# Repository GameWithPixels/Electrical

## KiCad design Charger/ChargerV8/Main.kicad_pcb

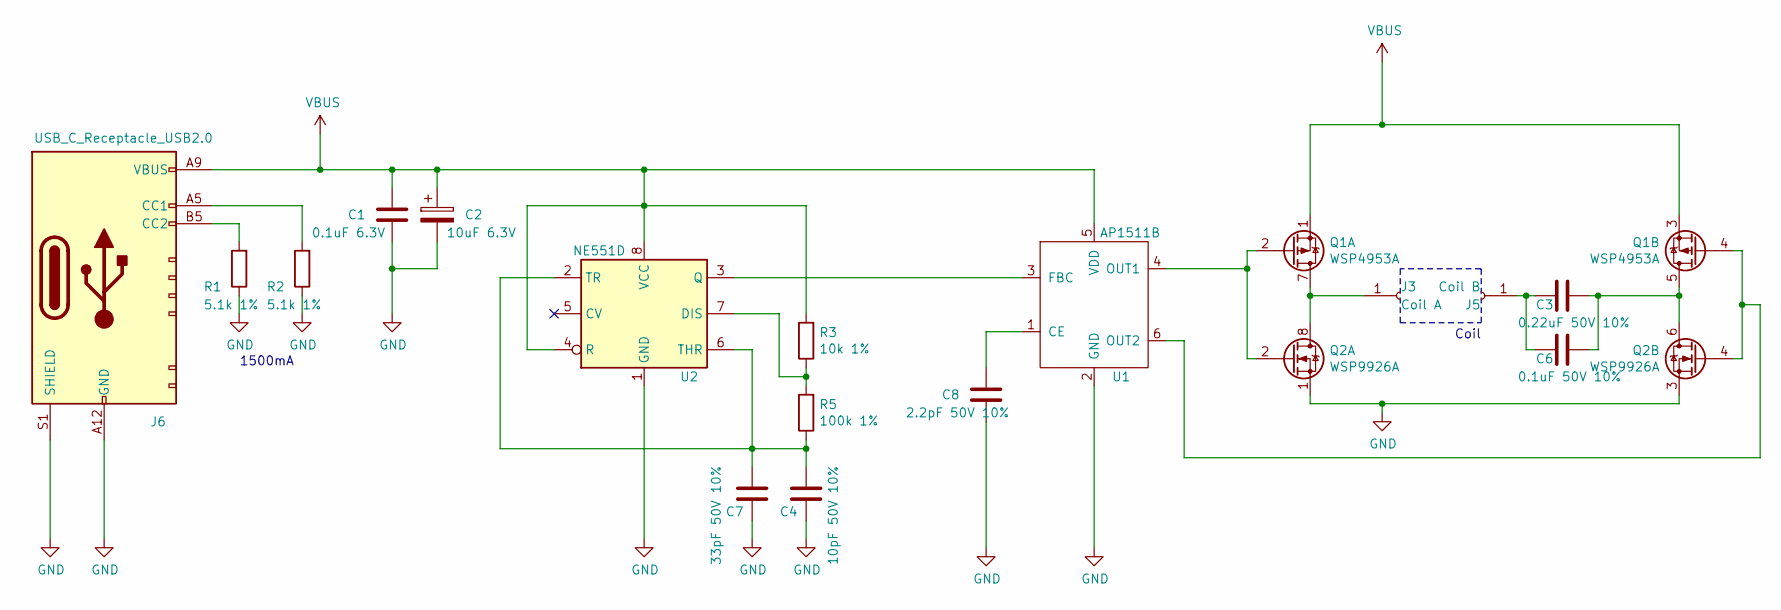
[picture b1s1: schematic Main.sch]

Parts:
C1: 0.1uF 6.3V; C_0603_1608Metric; Part Number TCC0603X7R104K500CT; LCSC Part Number C282519
C2: 10uF 6.3V; C_0603_1608Metric; Part Number CL10A106MP8NNNC; LCSC Part Number C85713
C3: 0.22uF 50V 10%; C_0805_2012Metric; Part Number CL21B224KBFNNNE; LCSC Part Number C5378
C4: 10pF 50V 10%; C_0603_1608Metric; Part Number CL10C100JB8NNNC; LCSC Part Number C1634
C6: 0.1uF 50V 10%; C_0805_2012Metric; Part Number CL21B104JBCNNNC; LCSC Part Number C62912
C7: 33pF 50V 10%; C_0603_1608Metric; Part Number CL10C330JB8NNNC; LCSC Part Number C1663
C8: 2.2pF 50V 10%; C_0603_1608Metric; Part Number CL10C2R2CB8NNNC; LCSC Part Number C84711
J3: Coil A; TestPoint_THTPad_D2.0mm_Drill1.0mm
J5: Coil B; TestPoint_THTPad_D2.0mm_Drill1.0mm
J6: USB_C_Receptacle_USB2.0; USB-C-SMD_10P-P1.00-L6.8-W8.9; Part Number TYPE-C-31-M-17; LCSC Part Number C283540
Q1: WSP4953A; SOP-8_3.9x4.9mm_P1.27mm; LCSC Part Number C148415
Q2: WSP9926A; SOP-8_3.9x4.9mm_P1.27mm; LCSC Part Number C86339
R1, R2: 5.1k 1%; R_0603_1608Metric; LCSC Part Number C23186
R3: 10k 1%; R_0603_1608Metric; LCSC Part Number C25804
R5: 100k 1%; R_0603_1608Metric; LCSC Part Number C25803
U1: AP1511B; SOT-26; LCSC Part Number C347457
U2: NE551D; SOP-8_3.9x4.9mm_P1.27mm; Part Number XL551; LCSC Part Number C707074

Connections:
GND: C1.2, C2.2, C4.2, C7.2, C8.2, J6.A12 (GND), J6.B12 (GND), J6.S1 (SHIELD), Q2.1 (S), Q2.3 (S), R1.1, R2.1, U1.2 (GND), U2.1 (GND)
unnamed: C3.1, C6.1, Q1.5 (D), Q1.6 (D), Q2.5 (D), Q2.6 (D)
unnamed: C3.2, C6.2, J5.1
unnamed: C4.1, C7.1, R5.1, U2.2 (TR), U2.6 (THR)
unnamed: C8.1, U1.1 (CE)
unnamed: J3.1, Q1.7 (D), Q1.8 (D), Q2.7 (D), Q2.8 (D)
unnamed: J6.A5 (CC1), R2.2
unnamed: J6.B5 (CC2), R1.2
unnamed: Q1.2 (G), Q2.2 (G), U1.4 (OUT1)
unnamed: Q1.4 (G), Q2.4 (G), U1.6 (OUT2)
unnamed: R3.1, R5.2, U2.7 (DIS)
unnamed: U1.3 (FBC), U2.3 (Q)
VBUS: C1.1, C2.1, J6.A9 (VBUS), J6.B9 (VBUS), Q1.1 (S), Q1.3 (S), R3.2, U1.5 (VDD), U2.4 (R), U2.8 (VCC)

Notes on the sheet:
1500mA
Coil

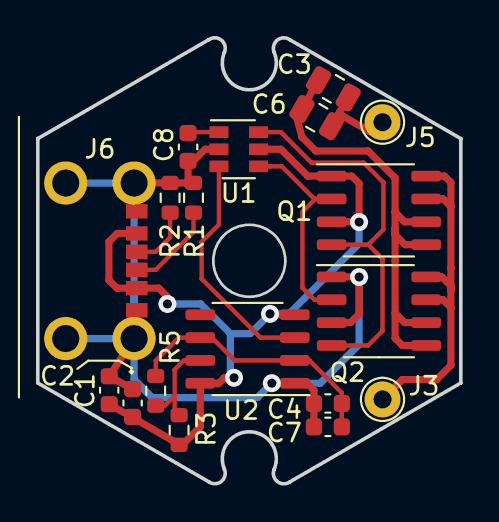
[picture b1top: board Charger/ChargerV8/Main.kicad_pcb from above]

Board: 2 copper layers, 23.5 x 24.8 mm, 18 parts (0 on the bottom side), 13 nets.

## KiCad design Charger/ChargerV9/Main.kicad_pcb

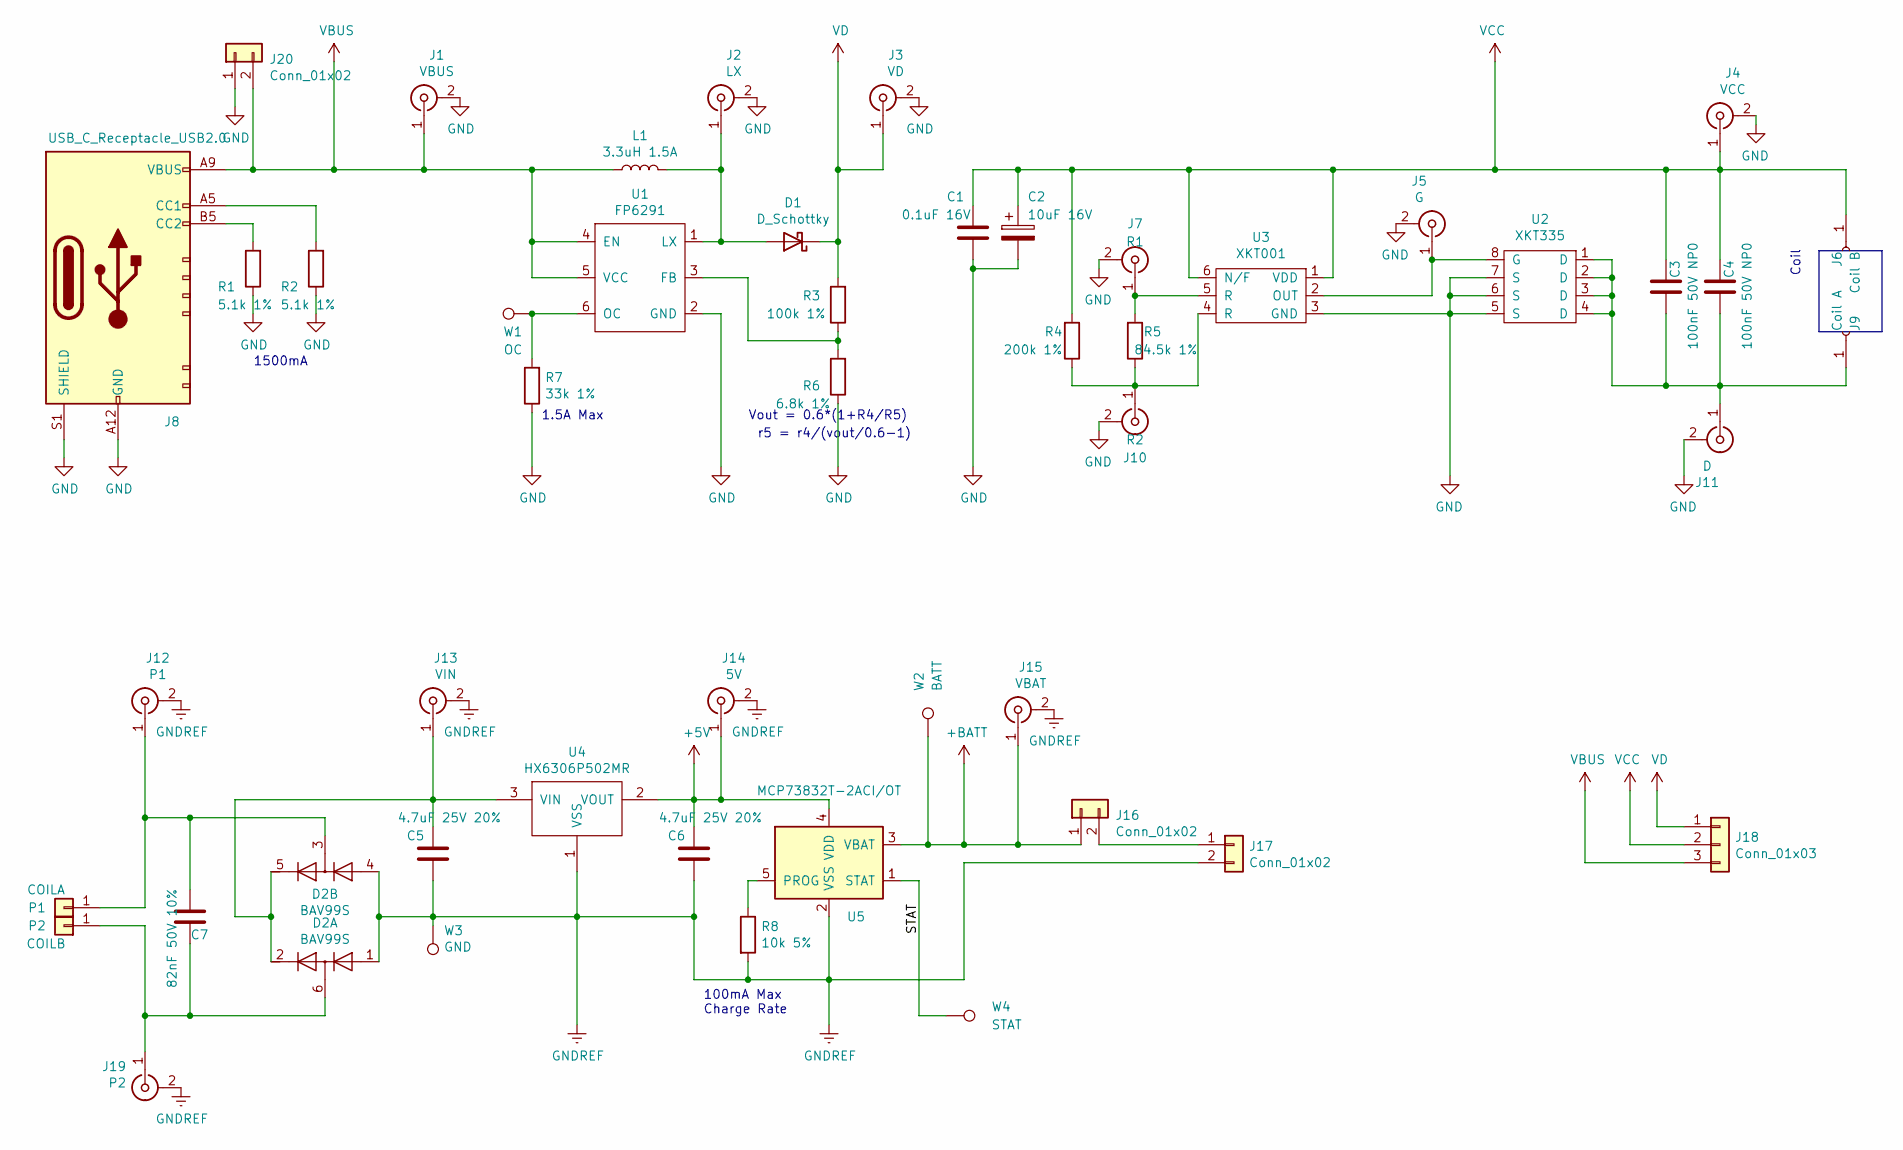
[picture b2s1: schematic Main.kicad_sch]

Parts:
C1: 0.1uF 16V; C_0402_1005Metric; Part Number C1005X5R1H104KT000F; LCSC Part Number C361202
C2: 10uF 16V; C_0805_2012Metric; LCSC Part Number C89827
C3, C4: 100nF 50V NP0; C_1206_3216Metric; Part Number 1206N104J500CT; LCSC Part Number C170182
C5, C6: 4.7uF 25V 20%; C_0805_2012Metric; Part Number CL21A475KAQNNNE; LCSC Part Number C1779
C7: 82nF 50V 10%; C_0805_2012Metric; Part Number CC0603KRX7R9BB823; LCSC Part Number C107100
D1: D_Schottky; D_SOD-123; Part Number B5819W; LCSC Part Number C8598
D2: BAV99S; SOT-363_SC-70-6; Part Number BAV99SH6327XTSA1; LCSC Part Number C68987
J1: VBUS; U.FL-R-SMT-1(80); Part Number U.FL-R-SMT-1(80); LCSC Part Number C88374
J2: LX; U.FL-R-SMT-1(80); Part Number U.FL-R-SMT-1(80); LCSC Part Number C88374
J3: VD; U.FL-R-SMT-1(80); Part Number U.FL-R-SMT-1(80); LCSC Part Number C88374
J4: VCC; U.FL-R-SMT-1(80); Part Number U.FL-R-SMT-1(80); LCSC Part Number C88374
J5: G; U.FL-R-SMT-1(80); Part Number U.FL-R-SMT-1(80); LCSC Part Number C88374
J6: Coil B; TestPoint_THTPad_D2.0mm_Drill1.0mm
J7: R1; U.FL-R-SMT-1(80); Part Number U.FL-R-SMT-1(80); LCSC Part Number C88374
J8: USB_C_Receptacle_USB2.0; USB-C-SMD_10P-P1.00-L6.8-W8.9; Part Number TYPE-C-31-M-17; LCSC Part Number C283540
J9: Coil A; TestPoint_THTPad_D2.0mm_Drill1.0mm
J10: R2; U.FL-R-SMT-1(80); Part Number U.FL-R-SMT-1(80); LCSC Part Number C88374
J11: D; U.FL-R-SMT-1(80); Part Number U.FL-R-SMT-1(80); LCSC Part Number C88374
J12: P1; U.FL-R-SMT-1(80); Part Number U.FL-R-SMT-1(80); LCSC Part Number C88374
J13: VIN; U.FL-R-SMT-1(80); Part Number U.FL-R-SMT-1(80); LCSC Part Number C88374
J14: 5V; U.FL-R-SMT-1(80); Part Number U.FL-R-SMT-1(80); LCSC Part Number C88374
J15: VBAT; U.FL-R-SMT-1(80); Part Number U.FL-R-SMT-1(80); LCSC Part Number C88374
J16, J20: Conn_01x02; PinHeader_1x02_P2.54mm_Vertical
J17: Conn_01x02; Hongjie 10100 Connector
J18: Conn_01x03; PinHeader_1x03_P2.54mm_Vertical
J19: P2; U.FL-R-SMT-1(80); Part Number U.FL-R-SMT-1(80); LCSC Part Number C88374
L1: 3.3uH 1.5A; L_1008_2520Metric; Part Number MPH252010C3R3MT; LCSC Part Number C370029
P1: COILA; TestPoint_THTPad_D1.5mm_Drill0.7mm
P2: COILB; TestPoint_THTPad_D1.5mm_Drill0.7mm
R1, R2: 5.1k 1%; R_0402_1005Metric; Part Number RC0402FR-075K1L; LCSC Part Number C105872
R3: 100k 1%; R_0402_1005Metric; Part Number 0402WGF1003TCE; LCSC Part Number C25741
R4: 200k 1%; R_0603_1608Metric; Part Number 0603WAF2003T5E; LCSC Part Number C25811
R5: 84.5k 1%; R_0603_1608Metric; Part Number ERJ3EKF8452V; LCSC Part Number C403376
R6: 6.8k 1%; R_0402_1005Metric; Part Number 0402WGF6801TCE; LCSC Part Number C25917
R7: 33k 1%; R_0402_1005Metric; Part Number 0402WGF3302TCE; LCSC Part Number C25779
R8: 10k 5%; R_0402_1005Metric; Part Number RC0402FR-0710KL; LCSC Part Number C60490
U1: FP6291; SOT-23-6; Part Number FP6291LR-G1; LCSC Part Number C18701
U2: XKT335; SO-8_3.9x4.9mm_P1.27mm
U3: XKT001; SOT-23-6
U4: HX6306P502MR; SOT-23; Part Number HX6306P502MR; LCSC Part Number C296209
U5: MCP73832T-2ACI/OT; SOT-23-5; Part Number MCP73832T-2ACI/OT; LCSC Part Number C38066
W1: OC; TestPoint_Pad_1.0x1.0mm
W2: BATT; TestPoint_Pad_1.0x1.0mm
W3: GND; TestPoint_Pad_1.0x1.0mm
W4: STAT; TestPoint_Pad_1.0x1.0mm

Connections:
+5V: C6.1, J14.1 (In), U4.2 (VOUT), U5.4 (VDD)
+BATT: J15.1 (In), J16.1, U5.3 (VBAT), W2.1
/STAT: U5.1 (STAT), W4.1
GND: C1.2, C2.2, J1.2 (Ext), J2.2 (Ext), J3.2 (Ext), J4.2 (Ext), J5.2 (Ext), J7.2 (Ext), J8.A12 (GND), J8.B12 (GND), J8.S1 (SHIELD), J10.2 (Ext), J11.2 (Ext), J20.1, R1.1, R2.1, R6.1, R7.1, U1.2 (GND), U2.5 (S), U2.6 (S), U2.7 (S), U3.3 (GND)
GNDREF: C5.2, C6.2, D2.1 (A1), D2.4 (A3), J12.2 (Ext), J13.2 (Ext), J14.2 (Ext), J15.2 (Ext), J17.2, J19.2 (Ext), R8.2, U4.1 (VSS), U5.2 (VSS), W3.1
unnamed: C3.1, C4.1, J9.1, J11.1 (In), U2.1 (D), U2.2 (D), U2.3 (D), U2.4 (D)
unnamed: C5.1, D2.2 (K2), D2.5 (K4), J13.1 (In), U4.3 (VIN)
unnamed: C7.1, D2.3 (K1A2), J12.1 (In), P1.1
unnamed: C7.2, D2.6 (K3A4), J19.1 (In), P2.1
unnamed: D1.2 (A), J2.1 (In), L1.2, U1.1 (LX)
unnamed: J5.1 (In), U2.8 (G), U3.2 (OUT)
unnamed: J7.1 (In), R5.2, U3.5 (R)
unnamed: J8.A5 (CC1), R2.2
unnamed: J8.B5 (CC2), R1.2
unnamed: J10.1 (In), R4.1, R5.1, U3.4 (R)
unnamed: J16.2, J17.1
unnamed: R3.1, R6.2, U1.3 (FB)
unnamed: R7.2, U1.6 (OC), W1.1
unnamed: R8.1, U5.5 (PROG)
VBUS: J1.1 (In), J8.A9 (VBUS), J8.B9 (VBUS), J18.3, J20.2, L1.1, U1.4 (EN), U1.5 (VCC)
VCC: C1.1, C2.1, C3.2, C4.2, J4.1 (In), J6.1, J18.2, R4.2, U3.1 (VDD), U3.6 (N/F)
VD: D1.1 (K), J3.1 (In), J18.1, R3.2

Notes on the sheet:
r5 = r4/(vout/0.6-1)
100mA Max Charge Rate
1.5A Max
1500mA
Vout = 0.6*(1+R4/R5)
Coil

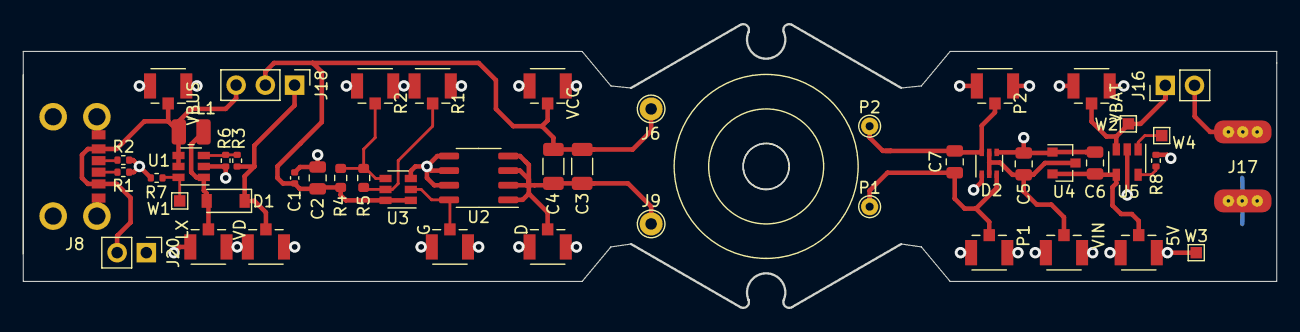
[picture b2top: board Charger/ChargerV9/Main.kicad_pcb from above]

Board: 2 copper layers, 109.0 x 24.7 mm, 49 parts (0 on the bottom side), 22 nets.

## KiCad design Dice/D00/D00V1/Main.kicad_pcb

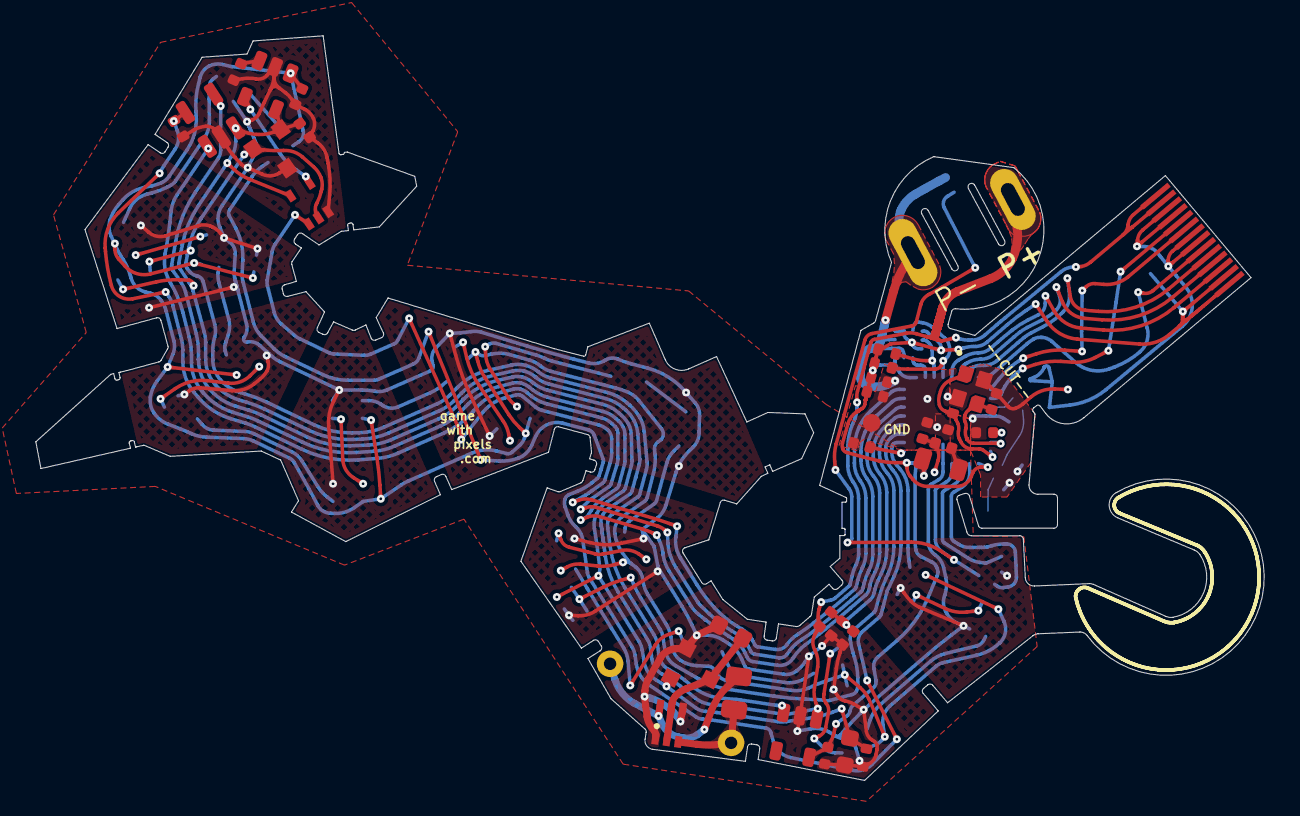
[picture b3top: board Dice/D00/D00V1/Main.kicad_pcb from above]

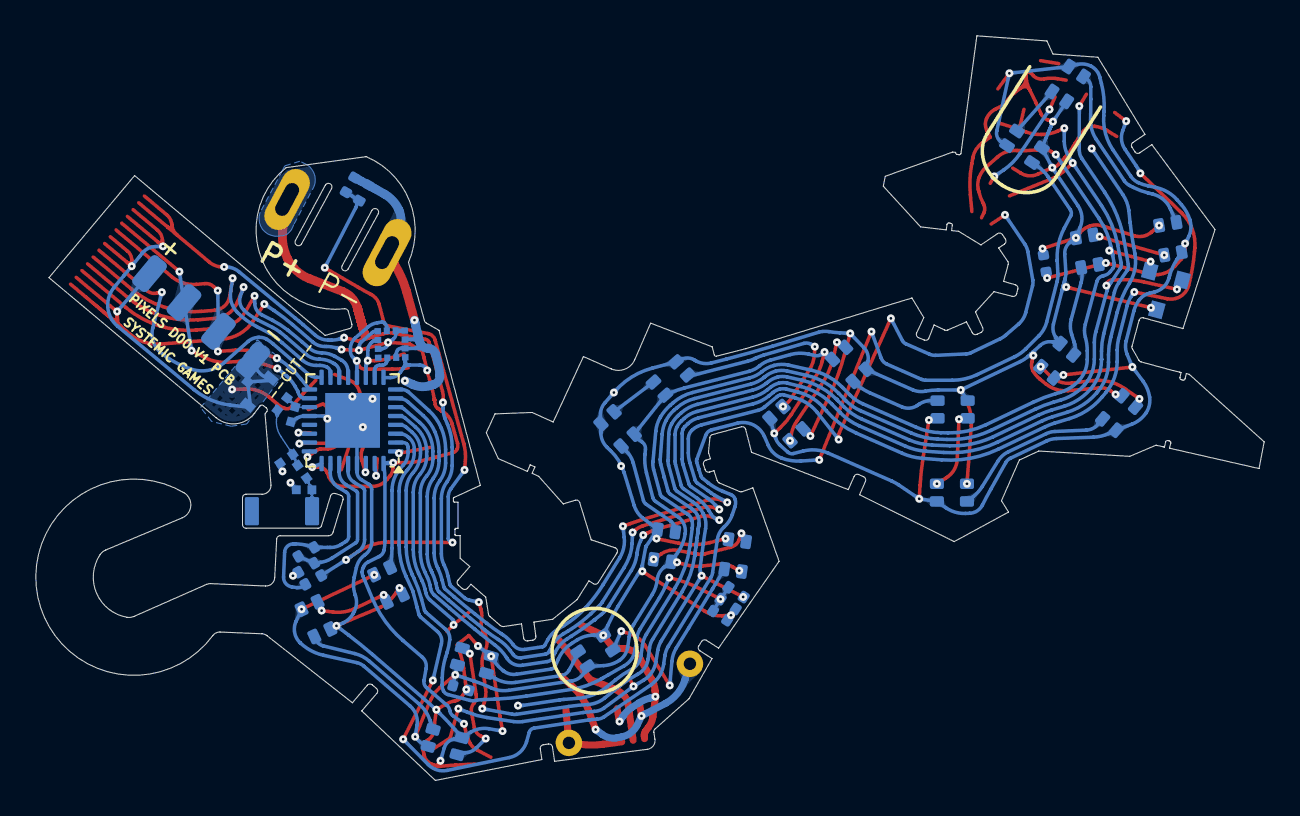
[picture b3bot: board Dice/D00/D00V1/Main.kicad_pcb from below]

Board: 2 copper layers, 69.4 x 42.1 mm, 76 parts (43 on the bottom side), 58 nets.

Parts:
AE1: Antenna_Chip; CHIP_ANT
C1, C4, C18: 4.7uF 10V 20%; C_0402_1005Metric
C2, C5: 8pF 10V 10%; C_0402_1005Metric
C3, C10, C23, C24: 0.1uF 10V 20%; C_0402_1005Metric
C6: DNP; C_0402_1005Metric
C7: 100pF NP0 10V 5%; C_0402_1005Metric
C8: 0.8pF 10V 5% C0G; 0402_RF
C9, C16: 10uF 10V 20%; C_0402_1005Metric
C11, C12: DNP; 0402_RF
C13: 4.7uF 25V 20%; C_0603_1608Metric
C15: 22uF 10V 20%; C_0603_1608Metric
C19: 12nF 50V 5% NP0; C_0805_2012Metric
C21, C22: 10nF 25V 10%; C_0402_1005Metric
D1: BAV99S; SOT-363_SC-70-6
D2, D3, D4, D5, D6, D7, D8, D9, D10, D11, D12, D13, D14, D15, D16, D17, D18, D20, D21: TX1812Z_2020
J1: Conn_01x14; FPC_14
J2: Conn_01x04; FPC-POGO-4
J3: Conn_01x02; Hongjie 10100 Connector
J4: DNP; MFH3.RECE.20369.001E.01
L1: 10uH 100mA 20%; L_0805_2012Metric
L2: 15nH 100mA 5%; L_0402_1005Metric
L3: 0 Ohm; 0402_RF
L5: 3.9nH 5%; 0402_RF
P5: COILA; TestPoint_THTPad_D1.5mm_Drill0.7mm
P6: COILB; TestPoint_THTPad_D1.5mm_Drill0.7mm
R1, R2, R7: 4.02M 1%; R_0402_1005Metric
R3: 10k 5%; R_0402_1005Metric
R4, R5, R10: 100k 1%; R_0402_1005Metric
R6: 22k 1%; R_0402_1005Metric
R8: 10M 1%; R_0402_1005Metric
R9: 220k 1%; R_0402_1005Metric
R12, R16: 2.7k 5%; R_0402_1005Metric
TH1: NTC 100k @ 25C; R_0402_1005Metric
U1: N52810_QFN32; QFN-32-1EP_5x5mm_P0.5mm_EP3.1x3.1mm
U2: KXTJ3-1057; LGA-12_2x2mm_P0.5mm
U3: PJ75BL50SA; SOT-23
U4: ME6215; SOT-23-5
U5: MCP73832T-2ACI/OT; SOT-23-5
U6: MT9700; SOT-23-5
U7: SN74LVC1G08; SOT-353_SC-70-5
U8, U8-alt1: VCS2373S; SOT-23
W19: GND; TEST_PIN
Y1: 32MHz 40ppm; Crystal_SMD_2016-4Pin_2.0x1.6mm

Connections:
+5V: C15.1, R1.1, R4.1, U3.2 (VOUT), U5.4 (VDD)
+BATT: C16.1, J1.1, J1.2, J3.1, R7.1, U4.1 (VIN), U5.3 (VBAT), U6.5 (VIN), U7.5 (VCC), U8.1 (VCC), U8-alt1.1 (VCC)
/5V_SENSE: C21.1, R1.2, R2.2, U1.4 (P0.04/AIN2)
/ACC_INT: U1.10 (P0.12), U2.5 (INT)
/ANTENNA: AE1.1 (FEED), C11.1, L3.2
/ANT_50: C12.1, J4.4 (RF), L3.1, L5.2
/ANT_NRF: C8.1, L5.1, U1.19 (ANT)
/BATT_NTC: C6.1, R5.2, TH1.1, U1.28 (P0.30/AIN6)
/LED_DATA: D2.1 (DIN), U1.2 (P0.00/XL1)
/LED_EN: U1.8 (P0.10), U7.1
/LED_RETURN: D12.3 (DOUT), U1.3 (P0.01/XL2)
/NTC_ID_VDD: R5.1, R10.2, U1.26 (P0.25)
/PROG: R6.1, U1.7 (P0.09), U5.5 (PROG)
/Power Supply/LED_EN_OUT: U6.4 (EN), U7.4
/Power Supply/MAG1_: U4.3 (CE), U7.2, U8.2 (OUT), U8-alt1.2 (OUT)
/SCL: R12.2, U1.12 (P0.15), U2.12 (SCL)
/SDA: R16.2, U1.11 (P0.14), U2.2 (SDA)
/STATS: U1.6 (P0.06), U5.1 (STAT)
/VBAT_SENSE: C22.1, R7.2, R8.1, U1.5 (P0.05/AIN3)
GND: C1.2, C2.1, C3.2, C4.2, C5.1, C6.2, C7.2, C8.2, C9.2, C10.2, C11.2, C12.2, C13.2, C15.2, C16.2, C18.2, C21.2, C22.2, C23.2, C24.2, D1.1 (A1), D1.4 (A3), D2.4 (GND), D3.4 (GND), D4.4 (GND), D5.4 (GND), D6.4 (GND), D7.4 (GND), D8.4 (GND), D9.4 (GND), D10.4 (GND), D11.4 (GND), D12.4 (GND), D13.4 (GND), D14.4 (GND), D15.4 (GND), D16.4 (GND), D17.4 (GND), D18.4 (GND), D20.4 (GND), D21.4 (GND), J1.3, J1.4, J1.7, J1.8, J2.4, J3.2, J4.1, J4.2, J4.3, R2.1, R3.2, R4.2, R6.2, R8.2, R9.1, TH1.2, U1.20 (VSS), U1.29 (VSS), U1.33 (VSS), U2.6 (GND), U2.8 (GND), U2.9 (GND), U3.1 (VSS), U4.2 (VSS), U5.2 (VSS), U6.2 (GND), U7.3 (GND), U8.3 (GND), U8-alt1.3 (GND), W19.1, Y1.2, Y1.4
unnamed: C19.2, D1.6 (K3A4), P6.1
unnamed: C19.1, D1.3 (K1A2), P5.1
unnamed: D2.3 (DOUT), D21.1 (DIN)
unnamed: D4.3 (DOUT), D5.1 (DIN)
unnamed: D10.1 (DIN), D14.3 (DOUT)
unnamed: D10.3 (DOUT), D13.1 (DIN)
unnamed: D11.1 (DIN), D13.3 (DOUT)
unnamed: D11.3 (DOUT), D12.1 (DIN)
unnamed: D9.3 (DOUT), D14.1 (DIN)
unnamed: D8.3 (DOUT), D15.1 (DIN)
unnamed: D9.1 (DIN), D15.3 (DOUT)
unnamed: D7.3 (DOUT), D16.1 (DIN)
unnamed: D8.1 (DIN), D16.3 (DOUT)
unnamed: D6.3 (DOUT), D17.1 (DIN)
unnamed: D7.1 (DIN), D17.3 (DOUT)
unnamed: D5.3 (DOUT), D18.1 (DIN)
unnamed: D6.1 (DIN), D18.3 (DOUT)
unnamed: D3.3 (DOUT), D20.1 (DIN)
unnamed: D4.1 (DIN), D20.3 (DOUT)
unnamed: D3.1 (DIN), D21.3 (DOUT)
unnamed: L1.2, L2.1
unnamed: L1.1, U1.31 (DCC)
unnamed: C3.1, U1.1 (DEC1)
unnamed: C7.1, U1.22 (DEC3)
unnamed: C1.1, L2.2, U1.30 (DEC4)
unnamed: R9.2, R10.1, U1.27 (P0.28/AIN4)
unnamed: C5.2, U1.23 (XC1), Y1.3
unnamed: C2.2, U1.24 (XC2), Y1.1
unnamed: R3.1, U6.3 (SET)
RESET: J1.9, U1.16 (P0.16)
RXI: J1.10, U1.15 (P0.20/TCLK)
SWDCLK: J1.6, J2.3, U1.17 (SWDCLK)
SWDIO: J1.5, J2.2, U1.18 (SWDIO)
SWO: J1.11, U1.14 (P0.18/TDATA0)
TXO: J1.12, U1.13 (P0.16/TDATA1)
VDC: C9.1, C23.1, C24.1, D2.2 (VCC), D3.2 (VCC), D4.2 (VCC), D5.2 (VCC), D6.2 (VCC), D7.2 (VCC), D8.2 (VCC), D9.2 (VCC), D10.2 (VCC), D11.2 (VCC), D12.2 (VCC), D13.2 (VCC), D14.2 (VCC), D15.2 (VCC), D16.2 (VCC), D17.2 (VCC), D18.2 (VCC), D20.2 (VCC), D21.2 (VCC), U6.1 (VOUT)
VDD: C4.1, C10.1, C18.1, J1.13, J1.14, J2.1, R12.1, R16.1, U1.9 (VDD), U1.25 (VDD), U1.32 (VDD), U2.1 (ADDR), U2.3 (IO_VDD), U2.7 (VDD), U2.10 (VDD), U2.11 (IO_VDD), U4.5 (VOUT)
VEE: C13.1, D1.2 (K2), D1.5 (K4), U3.3 (VIN)

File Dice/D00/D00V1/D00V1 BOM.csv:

"Reference","Value","Datasheet","Footprint","Qty","DNP","Manufacturer","Manufacturer Part Number"
"AE1","Antenna_Chip","~","Pixels-dice:CHIP_ANT","1","","Microgate","MGMA3216H2450-A02"
"C1,C4,C18","4.7uF 10V 20%","~","Pixels-dice:C_0402_1005Metric","3","","Murata","GRM155R61A475MEAAJ"
"C2,C5","8pF 10V 10%","~","Pixels-dice:C_0402_1005Metric","2","","Murata","GRT1555C2A8R0DA02"
"C3,C10,C23,C24","0.1uF 10V 20%","~","Pixels-dice:C_0402_1005Metric","4","","Murata","GRM155R61H104KE19D"
"C7","100pF NP0 10V 5%","~","Pixels-dice:C_0402_1005Metric","1","","Murata","GCM1555C1H101JA16J"
"C8","0.8pF 10V 5% C0G","~","Pixels-dice:0402_RF","1","","Murata","GJM1555C1HR80BB01"
"C9,C16","10uF 10V 20%","~","Pixels-dice:C_0402_1005Metric","2","","Murata","GRM155R60J106ME05D"
"C13","4.7uF 25V 20%","~","Capacitor_SMD:C_0603_1608Metric","1","","Murata","GRM188R61E475KE11D"
"C15","22uF 10V 20%","~","Capacitor_SMD:C_0603_1608Metric","1","","Murata","GRM188R61A226ME15D"
"C19","12nF 50V 5% NP0","","Capacitor_SMD:C_0805_2012Metric","1","","Murata","GRM2195C1H123JA01D"
"C21,C22","10nF 25V 10%","~","Pixels-dice:C_0402_1005Metric","2","","Murata","GRM155R71H103KA88"
"D1","BAV99S","https://assets.nexperia.com/documents/data-sheet/BAV99_SER.pdf","Package_TO_SOT_SMD:SOT-363_SC-70-6","1","","Nexperia","BAV99S,115"
"D2,D3,D4,D5,D6,D7,D8,D9,D10,D11,D12,D13,D14,D15,D16,D17,D18,D20,D21","TX1812Z_2020","","Pixels-dice:TX1812Z_2020","19","","TCWIN","TX1812Z 2020"
"L1","10uH 100mA 20%","~","Inductor_SMD:L_0805_2012Metric","1","","Murata","LQM21FN100M80L"
"L2","15nH 100mA 5%","~","Inductor_SMD:L_0402_1005Metric","1","","Murata","LQG15HS15NJ02D"
"L3","0 Ohm","~","Pixels-dice:0402_RF","1","","UNI-ROYAL(Uniroyal Elec)","0402WGJ0000TCE"
"L5","3.9nH 5%","~","Pixels-dice:0402_RF","1","","Murata","LQG15HS3N9B02D"
"R1,R2,R7","4.02M 1%","~","Resistor_SMD:R_0402_1005Metric","3","","UNI-ROYAL(Uniroyal Elec)","0402WGF4024TCE"
"R3","10k 5%","~","Resistor_SMD:R_0402_1005Metric","1","","UNI-ROYAL(Uniroyal Elec)","0402WGJ0103TCE"
"R4,R5,R10","100k 1%","~","-- mixed values --","3","","UNI-ROYAL(Uniroyal Elec)","0402WGF1003TCE"
"R6","18k 1%","~","Resistor_SMD:R_0402_1005Metric","1","","UNI-ROYAL(Uniroyal Elec)","0402WGF1802TCE"
"R8","10M 1%","~","Resistor_SMD:R_0402_1005Metric","1","","UNI-ROYAL(Uniroyal Elec)","0402WGF1005TCE"
"R9","220k 1%","~","Resistor_SMD:R_0402_1005Metric","1","","UNI-ROYAL(Uniroyal Elec)","0402WGF2203TCE"
"R12,R16","2.7k 5%","~","Resistor_SMD:R_0402_1005Metric","2","","UNI-ROYAL(Uniroyal Elec)","0402WGJ0272TCE"
"TH1","NTC 100k @ 25C","~","Pixels-dice:R_0402_1005Metric","1","","TDK","NTCG104EF104FT1X"
"U1","N52810_QFN32","","Package_DFN_QFN:QFN-32-1EP_5x5mm_P0.5mm_EP3.1x3.1mm","1","","Nordic Semiconductor","NRF52810-QCAA-R"
"U2","KXTJ3-1057","","Package_LGA:LGA-12_2x2mm_P0.5mm","1","","Kionix","KXTJ3-1057"
"U3","PJ75BL50SA","","Pixels-dice:SOT-23","1","","PJSEMI","PJ75BL50SA"
"U4","ME6215","","Pixels-dice:SOT-23-5","1","","MICRONE(Nanjing Micro One Elec)","ME6215C30M5G"
"U5","MCP73832T-2ACI/OT","http://ww1.microchip.com/downloads/en/DeviceDoc/20001984g.pdf","Package_TO_SOT_SMD:SOT-23-5","1","","Microchip","MCP73832T-2ACI/OT"
"U6","MT9700","","Pixels-dice:SOT-23-5","1","","XI'AN Aerosemi Tech","MT9700"
"U7","SN74LVC1G08","http://www.ti.com/lit/sg/scyt129e/scyt129e.pdf","Pixels-dice:SOT-353_SC-70-5","1","","UMW(Youtai Semiconductor Co., Ltd.)","SN74LVC1G08DCKR"
"U8","VCS2373S","","Pixels-dice:SOT-23","1","","HUAXIN","VCS2373S"
"Y1","32MHz 40ppm","~","Pixels-dice:Crystal_SMD_2016-4Pin_2.0x1.6mm","1","","Murata","XRCGB32M000F2P00R0"

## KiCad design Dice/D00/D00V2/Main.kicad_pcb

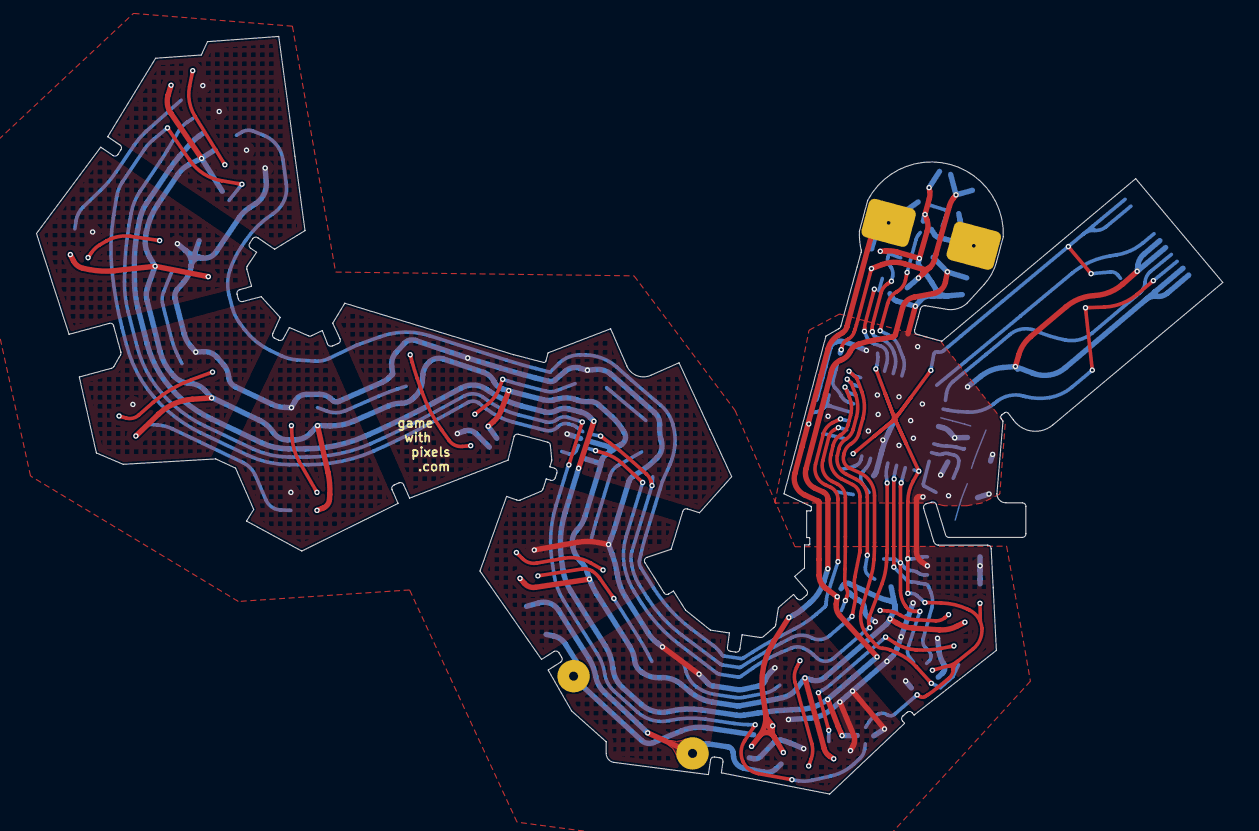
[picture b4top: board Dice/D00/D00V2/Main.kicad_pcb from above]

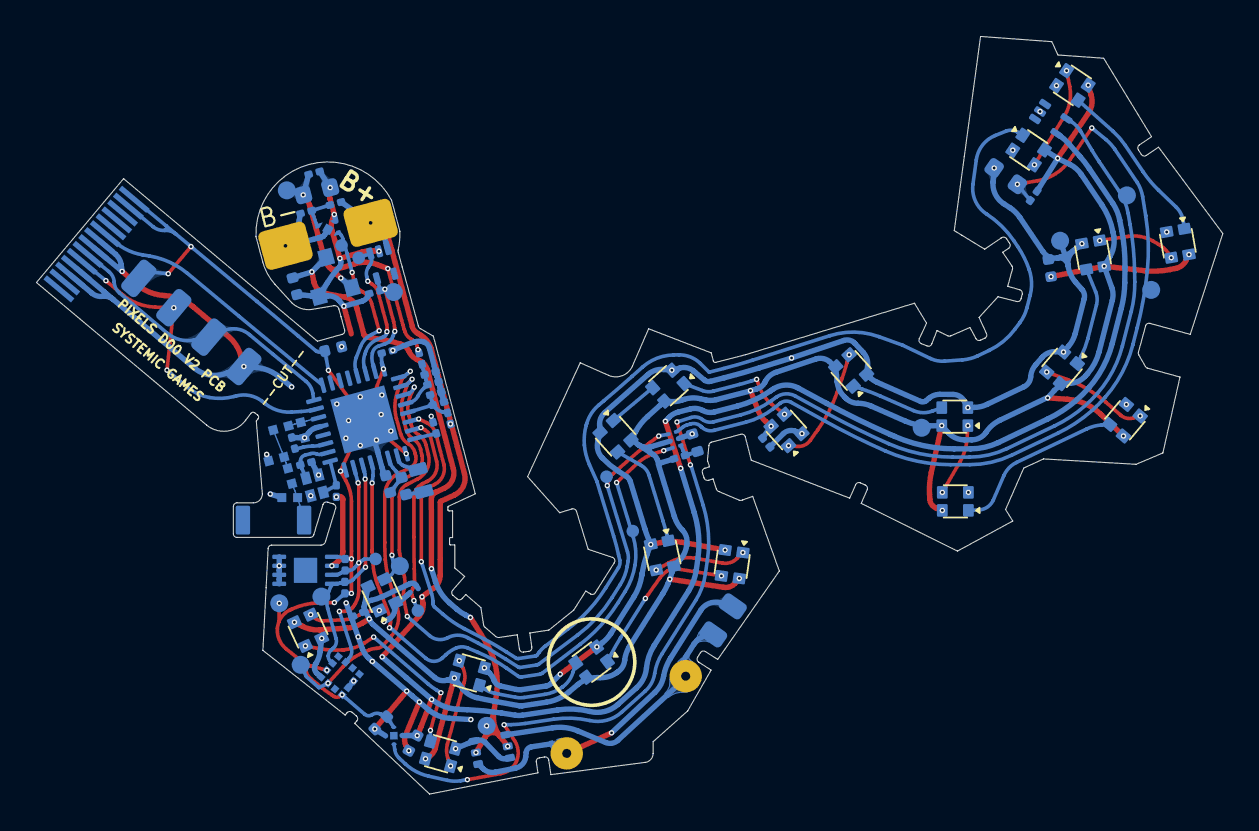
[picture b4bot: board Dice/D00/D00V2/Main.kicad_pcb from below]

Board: 2 copper layers, 65.9 x 42.1 mm, 92 parts (92 on the bottom side), 57 nets.

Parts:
AE1: Antenna_Chip; CHIP_ANT
C1, C4, C18: 4.7uF 10V 20%; C_0402_1005Metric
C2, C5: 8pF 10V 10%; C_0201_0603Metric
C3, C6, C10, C14, C23: 0.1uF 10V 20%; C_0201_0603Metric
C7: 100pF NP0 10V 2%; C_0201_0603Metric
C8: 0.8pF 10V 5% C0G; 0402_RF
C9, C16: 10uF 6.3V 20%; C_0402_1005Metric
C11, C12: DNP; 0402_RF
C13: 4.7uF 25V 20%; C_0402_1005Metric
C15: 22uF 10V 20%; C_0603_1608Metric
C19: 12nF 50V 5% NP0; C_0805_2012Metric
C21, C22: 10nF 25V 10%; C_0201_0603Metric
D1: BAV99S; SOT-363_SC-70-6
D2, D3, D4, D5, D6, D7, D8, D9, D10, D11, D12, D13, D14, D15, D16, D17, D18, D19, D20: TX1812MWCA5-F01
J1: Conn_01x14; FPC_14
J2: Conn_01x04; FPC-POGO-4
J3: Conn_01x02; Hongjie 10100 Solder Tabs
L1: 10uH 100mA 20%; C_1.2x1.8
L2: 15nH 100mA 5%; L_0402_1005Metric
L3: 0 Ohm; 0402_RF
L5: 3.9nH 5%; 0402_RF
P5: COILA; TestPoint_THTPad_D1.5mm_Drill0.7mm_nosilk
P6: COILB; TestPoint_THTPad_D1.5mm_Drill0.7mm_nosilk
Q1: ZSPT-Z1608C-06F-Z4; D_0603_1608Metric
R1, R2, R7: 3.9M 1%; R_0201_0603Metric
R4, R5: 10k 1%; R_0201_0603Metric
R6, R10, R11: 3.9k 1%; R_0201_0603Metric
R8: 10M 1%; R_0201_0603Metric
R9: 100k 1%; R_0201_0603Metric
R12: 510R 1%; R_0201_0603Metric
TH1: NTC 100k @ 25C; R_0402_1005Metric
U1: N52810_QFN32; QFN-32-1EP_5x5mm_P0.5mm_EP3.1x3.1mm
U2: SC7A20HTR; LGA-12_2x2mm_P0.5mm
U3: PJ75BL50SA; SOT-23
U4: ME6230; FPB1_1-4
U5: BL24C02F-NTRC; TDFN-8-1EP_3x2mm_P0.5mm_EP1.3x1.4mm
U6: AW35122
U7: DS6101; UDFN-4-1EP_1x1mm_P0.65mm_EP0.48x0.48mm
U8: SL1605; SOT-553
U9: XT4051; SOT-553
U10: WAS3157D-6/TR; DFN1109-6
W1: LED_DATA1; TEST_PIN
W2: PROG; TEST_PIN
W3: PHOTO; TEST_PIN
W4: VDC; TEST_PIN
W5: SM; TEST_PIN
W6: MAG1; TEST_PIN
W7: ACC_INT; TEST_PIN
W8: SCL; TEST_PIN
W9: SDA; TEST_PIN
W15: +5V; TEST_PIN
W16: VIN; TEST_PIN
W17: STAT; TEST_PIN
W19: GND; TEST_PIN
W21: LED2; TEST_PIN
W22: ADC_SELECT; TEST_PIN
W23: ADC_OUT; TEST_PIN
W25: VDD; TEST_PIN
Y1: 32MHz 40ppm; SX16Y032000B81T001

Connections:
+5V: C15.1, R1.1, R4.1, U3.2 (VOUT), U9.5 (VCC), W15.1
+BATT: C16.1, J3.1, R7.1, R12.1, U4.4 (VIN), U6.A2 (VIN), U8.4 (VDD), U9.1 (BAT)
/5V_SENSE: C21.1, R1.2, R2.2, U1.5 (P0.05/AIN3)
/ACC_INT: U1.8 (P0.10), U2.5 (INT1), W7.1
/ANTENNA: AE1.1 (FEED), C11.1, L3.2
/ANT_50: C12.1, L3.1, L5.2
/ANT_NRF: C8.1, L5.1, U1.19 (ANT)
/LED_DATA: D2.3 (DIN), U1.7 (P0.09), W1.1
/LED_EN: U1.2 (P0.00/XL1), U6.B2 (EN), W21.1
/LED_RETURN: D20.1 (DOUT), U1.3 (P0.01/XL2)
/MAG1_: U4.3 (CE), U8.5 (OUT), W6.1
/NTC_PHOTO_SENSE: U1.28 (P0.30/AIN6), U10.6 (A), W23.1
/OPT_A2D: Q1.1 (C), R5.2, U10.3 (B1), W3.1
/PROG: R6.1, U1.10 (P0.12), U9.4 (PROG), W2.1
/SCL: R10.2, U1.26 (P0.25), U2.12 (SCL), U5.6 (SCL), W8.1
/SDA: R11.2, U1.27 (P0.28/AIN4), U2.2 (SDA), U5.5 (SDA), W9.1
/SENSE_SELECT: U1.6 (P0.06), U10.4 (S), W22.1
/SM: U1.12 (P0.15), U7.3 (SM), W5.1
/STATS: U1.11 (P0.14), U9.3 (CHRG), W17.1
/VBAT_SENSE: C22.1, R7.2, R8.1, U1.4 (P0.04/AIN2)
/Wireless Charging/B-: C23.2, J3.2, U7.2 (VSS), U7.5 (PAD)
/Wireless Charging/COILA: C19.1, D1.3 (K1A2), P5.1
/Wireless Charging/COILB: C19.2, D1.6 (K3A4), P6.1
/Wireless Charging/TH1: R9.2, TH1.1, U10.1 (B0)
GND: C1.2, C2.1, C3.2, C4.2, C5.1, C6.2, C7.2, C8.2, C9.2, C10.2, C11.2, C12.2, C13.2, C14.2, C15.2, C16.2, C18.2, C21.2, C22.2, D1.1 (A1), D1.4 (A3), D2.2 (GND), D3.2 (GND), D4.2 (GND), D5.2 (GND), D6.2 (GND), D7.2 (GND), D8.2 (GND), D9.2 (GND), D10.2 (GND), D11.2 (GND), D12.2 (GND), D13.2 (GND), D14.2 (GND), D15.2 (GND), D16.2 (GND), D17.2 (GND), D18.2 (GND), D19.2 (GND), D20.2 (GND), J1.3, J1.4, J1.7, J1.8, J2.4, Q1.2 (E), R2.1, R4.2, R6.2, R8.2, TH1.2, U1.20 (VSS), U1.29 (VSS), U1.33 (VSS), U2.4 (NC), U2.8 (GND), U2.9 (GND), U3.1 (VSS), U4.2 (VSS), U5.1 (A0), U5.2 (A1), U5.3 (A2), U5.4 (GND), U5.7 (WP), U6.B1 (GND), U7.4 (EB-), U8.2 (GND), U9.2 (GND), U10.2 (GND), W19.1, Y1.2, Y1.4
unnamed: D2.1 (DOUT), D3.3 (DIN)
unnamed: D3.1 (DOUT), D4.3 (DIN)
unnamed: D4.1 (DOUT), D5.3 (DIN)
unnamed: D5.1 (DOUT), D6.3 (DIN)
unnamed: D6.1 (DOUT), D7.3 (DIN)
unnamed: D7.1 (DOUT), D8.3 (DIN)
unnamed: D8.1 (DOUT), D9.3 (DIN)
unnamed: D9.1 (DOUT), D10.3 (DIN)
unnamed: D10.1 (DOUT), D11.3 (DIN)
unnamed: D11.1 (DOUT), D12.3 (DIN)
unnamed: D12.1 (DOUT), D13.3 (DIN)
unnamed: D13.1 (DOUT), D14.3 (DIN)
unnamed: D14.1 (DOUT), D15.3 (DIN)
unnamed: D15.1 (DOUT), D16.3 (DIN)
unnamed: D16.1 (DOUT), D17.3 (DIN)
unnamed: D17.1 (DOUT), D18.3 (DIN)
unnamed: D18.1 (DOUT), D19.3 (DIN)
unnamed: D19.1 (DOUT), D20.3 (DIN)
unnamed: L1.2, L2.1
unnamed: L1.1, U1.31 (DCC)
unnamed: C3.1, U1.1 (DEC1)
unnamed: C7.1, U1.22 (DEC3)
unnamed: C1.1, L2.2, U1.30 (DEC4)
unnamed: C5.2, U1.23 (XC1), Y1.3
unnamed: C2.2, U1.24 (XC2), Y1.1
unnamed: C23.1, R12.2, U7.1 (BAT)
RESET: J1.9, U1.16 (P0.16)
SWDCLK: J1.6, J2.3, U1.17 (SWDCLK)
SWDIO: J1.5, J2.2, U1.18 (SWDIO)
VDC: C6.1, C9.1, C14.1, D2.4 (VCC), D3.4 (VCC), D4.4 (VCC), D5.4 (VCC), D6.4 (VCC), D7.4 (VCC), D8.4 (VCC), D9.4 (VCC), D10.4 (VCC), D11.4 (VCC), D12.4 (VCC), D13.4 (VCC), D14.4 (VCC), D15.4 (VCC), D16.4 (VCC), D17.4 (VCC), D18.4 (VCC), D19.4 (VCC), D20.4 (VCC), R5.1, R9.1, U6.A1 (VOUT), U10.5 (VCC), W4.1
VDD: C4.1, C10.1, C18.1, J1.13, J1.14, J2.1, R10.1, R11.1, U1.9 (VDD), U1.25 (VDD), U1.32 (VDD), U2.3 (IO_VDD), U2.7 (VDD), U4.1 (VOUT), U5.8 (VCC), W25.1
VEE: C13.1, D1.2 (K2), D1.5 (K4), U3.3 (VIN), W16.1
